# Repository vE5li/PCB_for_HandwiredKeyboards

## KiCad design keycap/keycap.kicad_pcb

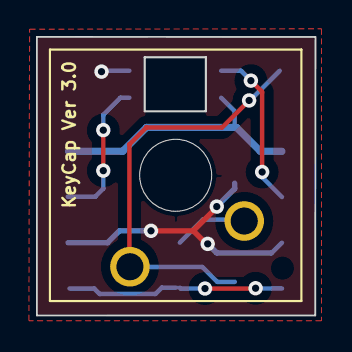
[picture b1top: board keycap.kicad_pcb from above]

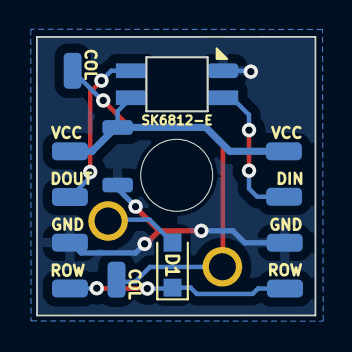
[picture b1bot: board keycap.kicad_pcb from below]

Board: 2 copper layers, 15.5 x 15.5 mm, 13 parts (12 on the bottom side), 7 nets.

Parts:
D1: 1N4148; D_SOD-323_HandSoldering
J1, J2, J3, J4, J5, J6, J7, J8, J9, J10: Conn_01x01_Female; SolderWirePad_1x01_SMD_1x2mm
SK6812-E: SK6812-MINI-E
SW1: SW_Push_Open; SW_Cherry_MX_1.00u_Plate

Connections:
/COL: J8.1, J9.1, SW1.1
/DIN: J2.1, SK6812-E.4
/DOUT: J5.1, SK6812-E.2
/ROW: D1.1, J7.1, J10.1
/VCC: J1.1, J4.1, SK6812-E.1
COL2ROW: D1.2, SW1.2
GND: J3.1, J6.1, SK6812-E.3

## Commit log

2024-09-21 Update design to use the SK6812-E
2024-09-21 Add gerber files
